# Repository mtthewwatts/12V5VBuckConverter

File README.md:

# 12V → 5V Buck Converter

A custom KiCad-designed buck (step-down) converter PCB that regulates an 11.4V–12V LiPo battery input down to a stable 5V/5A output. Designed to power a Raspberry Pi 5 and control electronics on an autonomous line-following search-and-rescue robot, consolidating the robot's entire power system into a single battery source.

Built for **MTE 380: Mechatronics Engineering Design Workshop** at the University of Waterloo (Group 12).

## Overview

The robot this board was built for is powered by a single 3S 11.4V LiPo battery. Rather than using a separate USB power bank to run the Raspberry Pi and control electronics, this PCB steps the battery voltage down to a regulated 5V/5A rail, cutting weight and wiring complexity. Raw battery voltage still feeds the drive motors directly through a separate motor shield.

- **Input:** 8V–40V (11.4V nominal, 3S LiPo)
- **Output:** 5V regulated, up to 5A continuous
- **Topology:** Synchronous-adjacent buck converter, datasheet reference design
- **Fabrication:** 1 oz copper, ~2mm power traces sized for 25W max output, continuous ground plane

## Key ICs / Components

| Reference | Part | Description |
|-----------|------|--------------|
| IC1 | LM2679SD-5.0/NOPB | 8V–40V, 5A Step-Down Switching Regulator (Texas Instruments) |
| D1 | VS-6TQ045S-M3 | 45V, 6A Schottky Diode — D2PAK (Vishay) |

Full bill of materials is documented in [`docs/Buck_Converter_Reference.docx`](docs/Buck_Converter_Reference.docx).

## Design Notes

This design follows Texas Instruments' [SNVA054C SIMPLE SWITCHER PCB Layout Guidelines](https://www.ti.com/lit/an/snva054c/snva054c.pdf) and the [LM2679 datasheet](https://www.ti.com/lit/ds/symlink/lm2679.pdf) reference application circuit. Key layout decisions:

- **Component placement** minimizes the high-current switching loop — regulator IC, inductor, diode, and capacitors are placed tightly together to reduce parasitic inductance.
- **Routing** keeps battery input and 5V output traces short and direct to limit voltage drop, with the switching node kept compact and isolated from signal traces to reduce noise coupling.
- **Ground plane** provides a low-impedance return path for both electrical stability and thermal performance.
- **Trace widths** (~2mm on high-current paths) were sized using IPC-2221 guidelines for a 5V/5A (25W) maximum load.

See [`docs/Buck_Converter_Reference.docx`](docs/Buck_Converter_Reference.docx) for the full design rationale, and Section 2.2.3 of [`docs/Milestone8_FinalReport.docx`](docs/Milestone8_FinalReport.docx) for how this board fits into the robot's overall electrical architecture.

## Project Files

| File | Purpose |
|------|---------|
| `12V5VBuckConverter.kicad_sch` | Schematic |
| `12V5VBuckConverter.kicad_pcb` | PCB layout |
| `12V5VBuckConverter.kicad_pro` | Project settings |
| `12V5VBuckConverter.step` | 3D STEP model |
| `ProjectLibrary.kicad_sym` | Project symbol library (LM2679) |
| `VS-6TQ045S-M3.kicad_sym` | Diode symbol |
| `VS6TQ045SM3.kicad_mod` | Diode footprint |
| `sym-lib-table` | Symbol library table |
| `fp-lib-table` | Footprint library table |

## Opening the Project

Open `12V5VBuckConverter.kicad_pro` in **KiCad 9.0** or later.

All custom libraries are stored in the project folder and referenced via `${KIPRJMOD}`, so no path changes are needed after cloning.

```bash
git clone https://github.com/<your-username>/<your-repo>.git
cd <your-repo>
# then open 12V5VBuckConverter.kicad_pro in KiCad
```

## Status / Known Limitations

- Validated on the bench and used successfully on Game Day, but battery voltage sag under load was not fully characterized — output behavior at low state-of-charge is a known open item.
- No onboard reverse-polarity or overcurrent protection beyond the regulator IC's internal limiting.
- Designed for a single fixed 5V/5A rail; not currently configurable for other output voltages.

## Background

This board was the electrical subsystem of a larger capstone project: a fully autonomous line-following robot built to navigate a maze, retrieve a target, and return it to a safe zone under a $300 budget and strict size/weight constraints. Full project report and results are in [`docs/Milestone8_FinalReport.docx`](docs/Milestone8_FinalReport.docx).

## License

MIT — see [LICENSE](LICENSE).

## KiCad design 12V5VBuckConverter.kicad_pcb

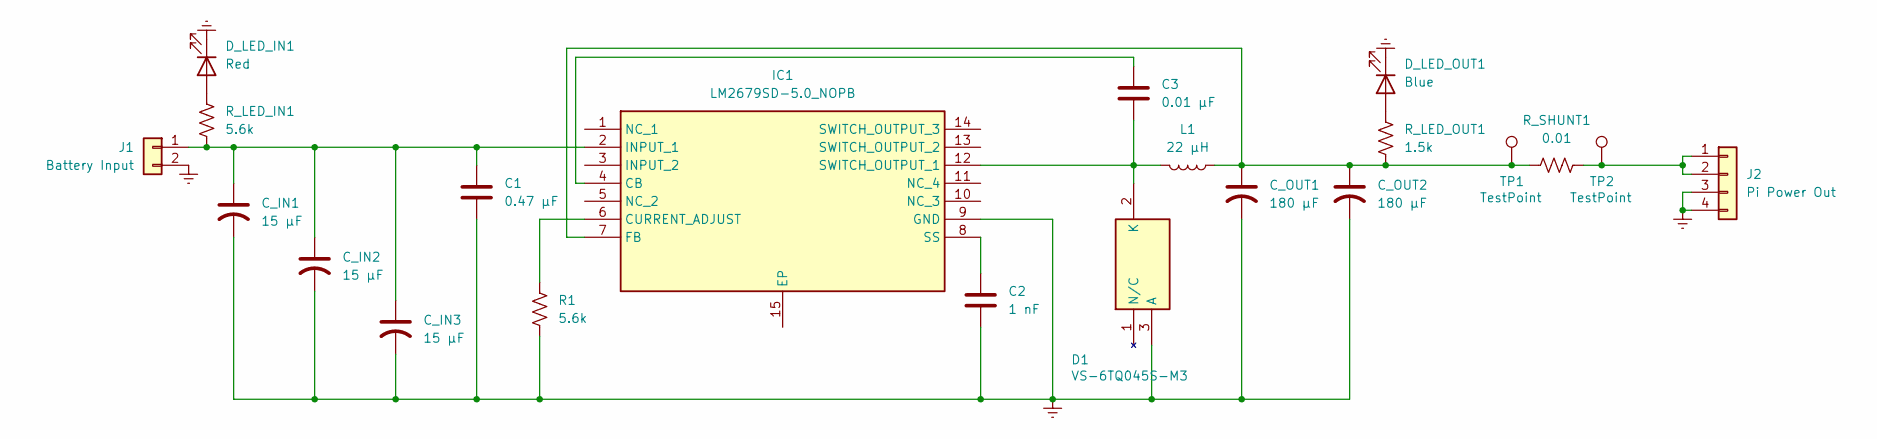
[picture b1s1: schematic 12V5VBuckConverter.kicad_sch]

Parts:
C1: 0.47 μF; C_0805_2012Metric
C2: 1 nF; C_0805_2012Metric
C3: 0.01 μF; C_0805_2012Metric
C_IN1, C_IN2, C_IN3: 15 μF; C_1210_3225Metric
C_OUT1, C_OUT2: 180 μF; CP_Elec_8x10
D1: VS-6TQ045S-M3; VS6TQ045SM3; Mouser Part Number 78-VS-6TQ045S-M3
D_LED_IN1: Red; LED_0805_2012Metric
D_LED_OUT1: Blue; LED_0805_2012Metric
IC1: LM2679SD-5.0_NOPB; SON80P500X600X100-15N; Mouser Part Number 926-LM2679SD50NOPB
J1: Battery Input; TerminalBlock_Phoenix_MKDS-1,5-2-5.08_1x02_P5.08mm_Horizont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
J2: Pi Power Out; TerminalBlock_Phoenix_MKDS-1,5-4-5.08_1x04_P5.08mm_Horizont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
L1: 22 μH; L_7.3x7.3_H4.5
R1: 5.6k; R_0805_2012Metric
R_LED_IN1: 5.6k; R_0805_2012Metric
R_LED_OUT1: 1.5k; R_0805_2012Metric
R_SHUNT1: 0.01; R_2512_6332Metric
TP1, TP2: TestPoint; TestPoint_Pad_D2.0mm

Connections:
GND\: C1.2, C2.2, C_IN1.2, C_IN2.2, C_IN3.2, C_OUT1.2, C_OUT2.2, D1.3 (A), D_LED_IN1.1 (K), D_LED_OUT1.1 (K), IC1.9 (GND), IC1.15 (EP), J1.2, J2.3, J2.4, R1.2
unnamed: C3.2, D1.2 (K), IC1.12 (SWITCH_OUTPUT_1), L1.2
unnamed: D_LED_IN1.2 (A), R_LED_IN1.1
unnamed: D_LED_OUT1.2 (A), R_LED_OUT1.1
unnamed: C3.1, IC1.4 (CB)
unnamed: IC1.6 (CURRENT_ADJUST), R1.1
unnamed: C_OUT1.1, C_OUT2.1, IC1.7 (FB), L1.1, R_LED_OUT1.2, R_SHUNT1.1, TP1.1
unnamed: C1.1, C_IN1.1, C_IN2.1, C_IN3.1, IC1.2 (INPUT_1), J1.1, R_LED_IN1.2
unnamed: C2.1, IC1.8 (SS)
unnamed: J2.1, J2.2, R_SHUNT1.2, TP2.1

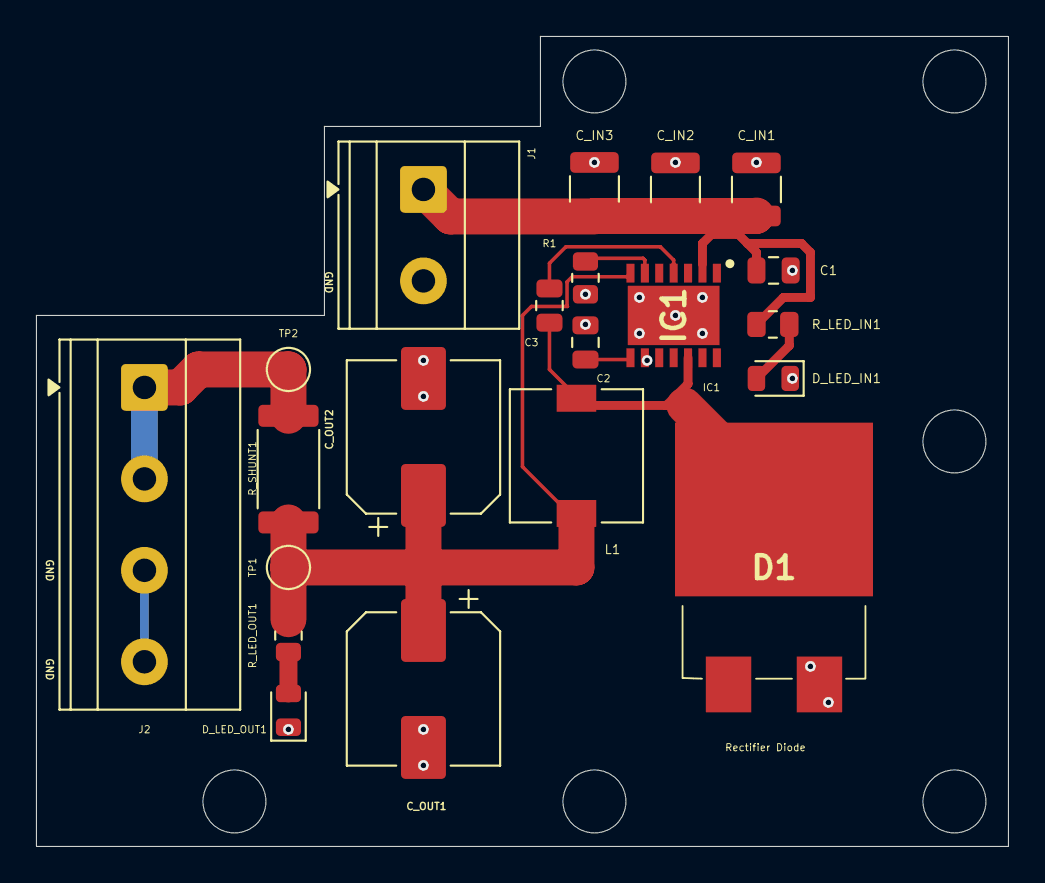
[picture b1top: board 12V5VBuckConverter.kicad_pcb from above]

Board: 2 copper layers, 54.0 x 45.0 mm, 27 parts (0 on the bottom side), 10 nets.

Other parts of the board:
MH1, MH2, MH3, MH4, MH5, MH6: MountingHole_3mm

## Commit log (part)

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2026-06-13 Full Upload
